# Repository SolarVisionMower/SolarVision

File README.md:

# SolarVision Mower

> [!NOTE]
> *This project is still in development!*

## Project Overview

SolarVision Mower is a YOLO and LiDAR based autonomous lawnmower that we're building for our final capstone engineering project. Once complete, it will feature *fully custom hardware and software*, which includes custom circuitry, firmware, 3D printed or welded components, a modified frame from an existing TORO lawnmower, and much more.

To stay up-to-date with the latest developments, check out the [dev/general][01] branch (specifically the [BACKLOG.md][02] file), to find a detailed list of everything we're doing. It will also help to navigate the various branches and directories (which will most likely grow in complexity as time progresses). Branches will the naming convention `xx/yy` are *permanent* branches, in the category specified by `xx`. Others can be considered temporary only.

## Tech Stack

- Software Tools
    - **KiCAD** - For PCB Design
    - **Fusion360** - For designing 3D models
    - **ESP-IDF** - For firmware programming on the ESP32
    - **STM32CubeMX** - For hardware configuration and initial code generation on the STM32
    - **STM32CubeIDE** - For firmware programming on the STM32
    - **ST Edge AI Suite** - For YOLO model conversion and code generation
- Software Libraries
    - **FreeRTOS** - For multithreading on both microcontrollers
    - **[espressif/arduino-esp32][05]** - For running Arduino functions in the ESP32
    - **[thijses/rplidar][06]** - For ease of integration of the RPLidar A1.
    - **[jh247247/DW1000-fan-video][07]** - Initial firmware implementation for the Ultra Wideband Positioning Modules
- Hardware Tools
    - Fabrication tools from the [NJIT Makerspace][08].
    - Circuit analysis tools from the [NJIT ECE Labs][09].
    - SLogic16U3 Logic Analyzer.
    - [JLCPCB][10] for PCB fabrication

## The Team

- Arnav Revankar
    - **Computer Engineer** - Graduating Dec 2026
    - Responsibilities:
        - Co-Lead Developer, and Manager for Hardware Design.
        - Developed the [STM32N6 Board][03]
        - Oversaw the development of the [Main Board][04]
- Panuha Were
    - **Computer Engineer** - Graduating May 2026
    - Responsibilities:
        - Co-Lead Developer, and Manager for Software Design
        - Contributed to the [Main Board][04] hardware design
        - Overseeing Firmware Development for the ESP32S3
- Layth Younes 
    - **Computer Engineer** - Graduating May 2026
    - Responsibilities:
        - Developer, and Manager for 3D Designs and Fabrication
        - Contributed to the [Main Board][04] hardware design
        - Overseeing the physical design of the frame, and enclosures.
- Daniel Assaf
    - **Computer Engineer** - Graduating May 2026
    - Responsibilities:
        - Developer, and Test/Integration Engineer
        - Contributed to the [Main Board][04] hardware design
        - Contributed to writing Documentation/Reports on progress.

## License

As of date (March 2nd, 2026) we have *not* decided upon a license. All rights are reserved by the authors.

<!-- Links -->
[01]: https://github.com/SolarVision/SolarVisionMower/tree/dev/general
[02]: https://github.com/SolarVision/SolarVisionMower/blob/dev/general/docs/BACKLOG.md
[03]: https://github.com/SolarVision/SolarVisionMower/tree/dev/PCBDesign/Hardware/STM32N6_Board
[04]: https://github.com/SolarVision/SolarVisionMower/tree/dev/MainBoard/Hardware/Main_Board
[05]: https://github.com/espressif/arduino-esp32
[06]: https://github.com/thijses/rplidar
[07]: https://github.com/jh247247/DW1000-fan-video
[08]: https://njitmakerspace.com
[09]: https://ecelabs.njit.edu
[10]: https://jlcpcb.com

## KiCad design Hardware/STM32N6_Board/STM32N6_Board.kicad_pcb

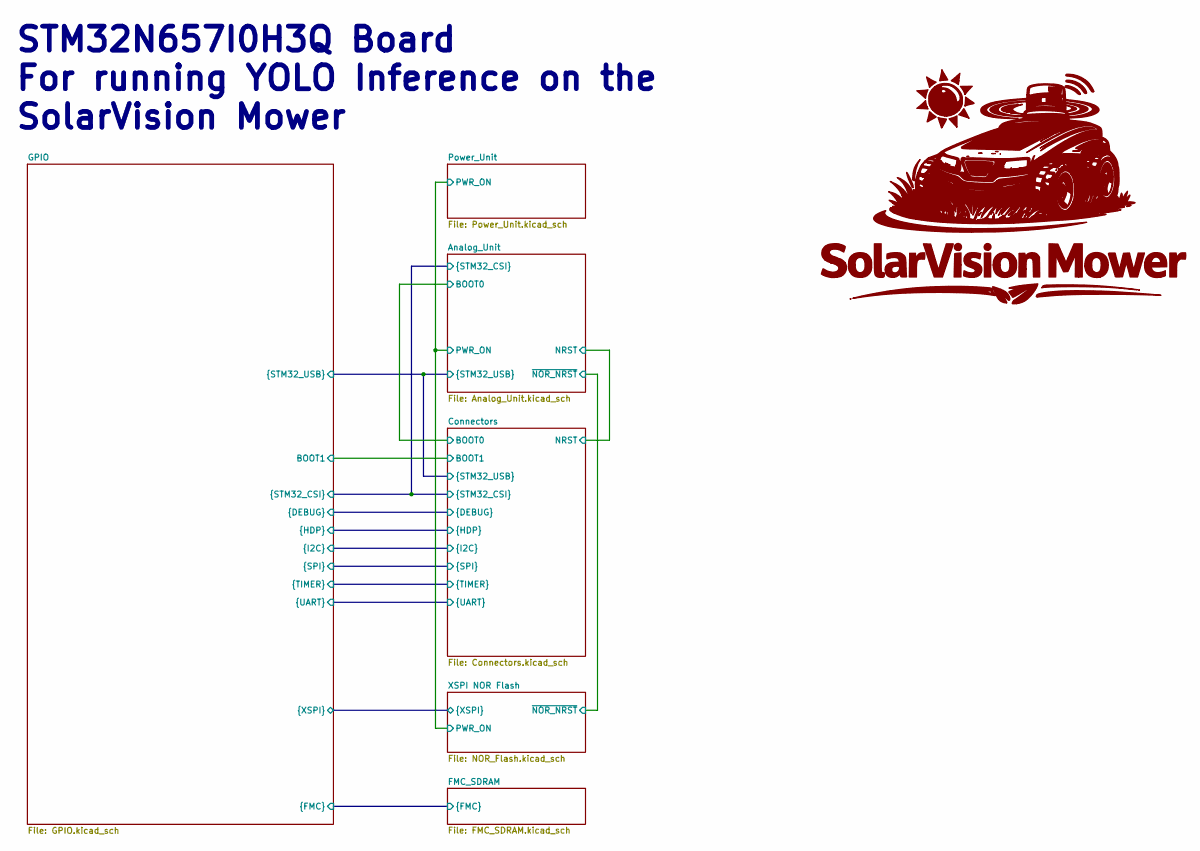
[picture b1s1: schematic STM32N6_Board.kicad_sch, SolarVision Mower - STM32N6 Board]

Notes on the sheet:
STM32N657I0H3Q Board For running YOLO Inference on the SolarVision Mower

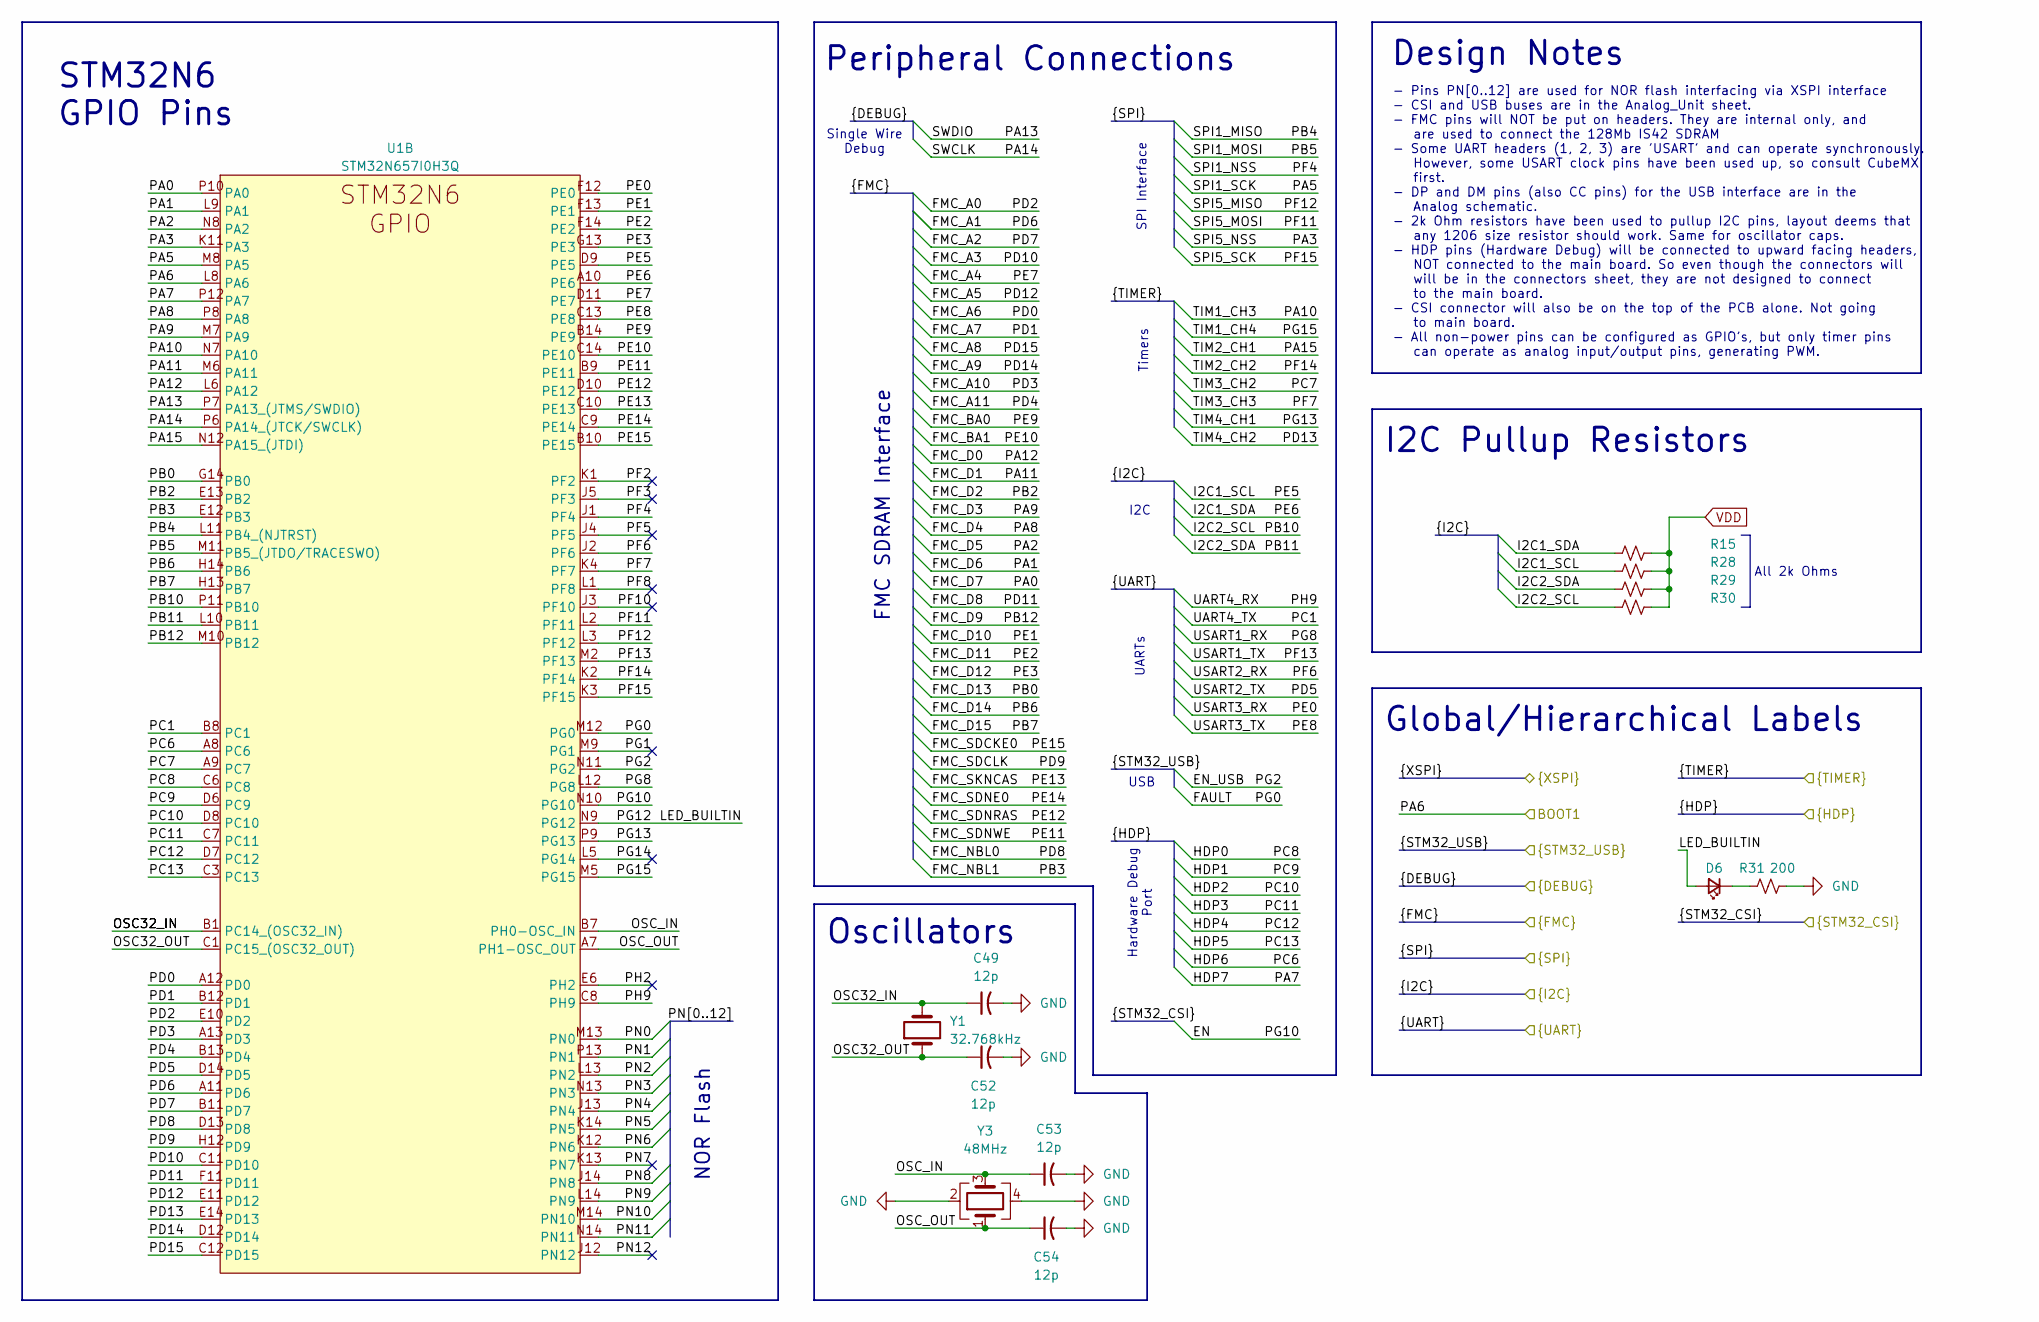
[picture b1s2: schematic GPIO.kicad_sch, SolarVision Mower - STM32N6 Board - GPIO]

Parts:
C49, C52, C53, C54: 12p; C_0402_1005Metric_Pad0.74x0.62mm_HandSolder
D6: LED_Small; LED_0603_1608Metric_Pad1.05x0.95mm_HandSolder
R15, R28, R29, R30: 2k; R_0402_1005Metric
R31: 200; R_0402_1005Metric
U1: STM32N657I0H3Q; STM32N657I0H3Q_VFBGA178_14x14
Y1: 32.768kHz; 32kHz_SC-20S_2Pin_2.05x1.2mm
Y3: 48MHz; 48MHz_Q22FA12800150_4Pin_2.0z1.6mm

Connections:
/Analog_Unit/EN: U1.N10 (PG10); also elsewhere on the board
/Analog_Unit/EN_USB: U1.N11 (PG2); also elsewhere on the board
/Analog_Unit/FAULT: U1.M12 (PG0); also elsewhere on the board
/Connectors/BOOT1: U1.L8 (PA6); also elsewhere on the board
/Connectors/HDP0: U1.C6 (PC8); also elsewhere on the board
/Connectors/HDP1: U1.D6 (PC9); also elsewhere on the board
/Connectors/HDP2: U1.D8 (PC10); also elsewhere on the board
/Connectors/HDP3: U1.C7 (PC11); also elsewhere on the board
/Connectors/HDP4: U1.D7 (PC12); also elsewhere on the board
/Connectors/HDP5: U1.C3 (PC13); also elsewhere on the board
/Connectors/HDP6: U1.A8 (PC6); also elsewhere on the board
/Connectors/HDP7: U1.P12 (PA7); also elsewhere on the board
/Connectors/I2C1_SCL: R28.1, U1.D9 (PE5); also elsewhere on the board
/Connectors/I2C1_SDA: R15.1, U1.A10 (PE6); also elsewhere on the board
/Connectors/I2C2_SCL: R30.1, U1.P11 (PB10); also elsewhere on the board
/Connectors/I2C2_SDA: R29.1, U1.L10 (PB11); also elsewhere on the board
/Connectors/SPI1_MISO: U1.L11 (PB4_(NJTRST)); also elsewhere on the board
/Connectors/SPI1_MOSI: U1.M11 (PB5_(JTDO/TRACESWO)); also elsewhere on the board
/Connectors/SPI1_NSS: U1.J1 (PF4); also elsewhere on the board
/Connectors/SPI1_SCK: U1.M8 (PA5); also elsewhere on the board
/Connectors/SPI5_MISO: U1.L3 (PF12); also elsewhere on the board
/Connectors/SPI5_MOSI: U1.L2 (PF11); also elsewhere on the board
/Connectors/SPI5_NSS: U1.K11 (PA3); also elsewhere on the board
/Connectors/SPI5_SCK: U1.K3 (PF15); also elsewhere on the board
/Connectors/SWCLK: U1.P6 (PA14_(JTCK/SWCLK)); also elsewhere on the board
/Connectors/SWDIO: U1.P7 (PA13_(JTMS/SWDIO)); also elsewhere on the board
/Connectors/TIM1_CH3: U1.N7 (PA10); also elsewhere on the board
/Connectors/TIM1_CH4: U1.M5 (PG15); also elsewhere on the board
/Connectors/TIM2_CH1: U1.N12 (PA15_(JTDI)); also elsewhere on the board
/Connectors/TIM2_CH2: U1.K2 (PF14); also elsewhere on the board
/Connectors/TIM3_CH2: U1.A9 (PC7); also elsewhere on the board
/Connectors/TIM3_CH3: U1.K4 (PF7); also elsewhere on the board
/Connectors/TIM4_CH1: U1.P9 (PG13); also elsewhere on the board
/Connectors/TIM4_CH2: U1.E14 (PD13); also elsewhere on the board
/Connectors/UART4_RX: U1.C8 (PH9); also elsewhere on the board
/Connectors/UART4_TX: U1.B8 (PC1); also elsewhere on the board
/Connectors/USART1_RX: U1.L12 (PG8); also elsewhere on the board
/Connectors/USART1_TX: U1.M2 (PF13); also elsewhere on the board
/Connectors/USART2_RX: U1.J2 (PF6); also elsewhere on the board
/Connectors/USART2_TX: U1.D14 (PD5); also elsewhere on the board
/Connectors/USART3_RX: U1.F12 (PE0); also elsewhere on the board
/Connectors/USART3_TX: U1.C13 (PE8); also elsewhere on the board
/FMC_SDRAM/FMC_A0: U1.E10 (PD2); also elsewhere on the board
/FMC_SDRAM/FMC_A1: U1.A11 (PD6); also elsewhere on the board
/FMC_SDRAM/FMC_A2: U1.B11 (PD7); also elsewhere on the board
/FMC_SDRAM/FMC_A3: U1.C11 (PD10); also elsewhere on the board
/FMC_SDRAM/FMC_A4: U1.D11 (PE7); also elsewhere on the board
/FMC_SDRAM/FMC_A5: U1.E11 (PD12); also elsewhere on the board
/FMC_SDRAM/FMC_A6: U1.A12 (PD0); also elsewhere on the board
/FMC_SDRAM/FMC_A7: U1.B12 (PD1); also elsewhere on the board
/FMC_SDRAM/FMC_A8: U1.C12 (PD15); also elsewhere on the board
/FMC_SDRAM/FMC_A9: U1.D12 (PD14); also elsewhere on the board
/FMC_SDRAM/FMC_A10: U1.A13 (PD3); also elsewhere on the board
/FMC_SDRAM/FMC_A11: U1.B13 (PD4); also elsewhere on the board
/FMC_SDRAM/FMC_BA0: U1.B14 (PE9); also elsewhere on the board
/FMC_SDRAM/FMC_BA1: U1.C14 (PE10); also elsewhere on the board
/FMC_SDRAM/FMC_D0: U1.L6 (PA12); also elsewhere on the board
/FMC_SDRAM/FMC_D1: U1.M6 (PA11); also elsewhere on the board
/FMC_SDRAM/FMC_D2: U1.E13 (PB2); also elsewhere on the board
/FMC_SDRAM/FMC_D3: U1.M7 (PA9); also elsewhere on the board
/FMC_SDRAM/FMC_D4: U1.P8 (PA8); also elsewhere on the board
/FMC_SDRAM/FMC_D5: U1.N8 (PA2); also elsewhere on the board
/FMC_SDRAM/FMC_D6: U1.L9 (PA1); also elsewhere on the board
/FMC_SDRAM/FMC_D7: U1.P10 (PA0); also elsewhere on the board
/FMC_SDRAM/FMC_D8: U1.F11 (PD11); also elsewhere on the board
/FMC_SDRAM/FMC_D9: U1.M10 (PB12); also elsewhere on the board
/FMC_SDRAM/FMC_D10: U1.F13 (PE1); also elsewhere on the board
/FMC_SDRAM/FMC_D11: U1.F14 (PE2); also elsewhere on the board
/FMC_SDRAM/FMC_D12: U1.G13 (PE3); also elsewhere on the board
/FMC_SDRAM/FMC_D13: U1.G14 (PB0); also elsewhere on the board
/FMC_SDRAM/FMC_D14: U1.H14 (PB6); also elsewhere on the board
/FMC_SDRAM/FMC_D15: U1.H13 (PB7); also elsewhere on the board
/FMC_SDRAM/FMC_NBL0: U1.D13 (PD8); also elsewhere on the board
/FMC_SDRAM/FMC_NBL1: U1.E12 (PB3); also elsewhere on the board
/FMC_SDRAM/FMC_SDCKE0: U1.B10 (PE15); also elsewhere on the board
/FMC_SDRAM/FMC_SDCLK: U1.H12 (PD9); also elsewhere on the board
/FMC_SDRAM/FMC_SDNE0: U1.C9 (PE14); also elsewhere on the board
/FMC_SDRAM/FMC_SDNRAS: U1.D10 (PE12); also elsewhere on the board
/FMC_SDRAM/FMC_SDNWE: U1.B9 (PE11); also elsewhere on the board
/FMC_SDRAM/FMC_SKNCAS: U1.C10 (PE13); also elsewhere on the board
/GPIO/LED_BUILTIN: D6.2 (A), U1.N9 (PG12)
/GPIO/OSC32_IN: C49.1, U1.B1 (PC14_(OSC32_IN)), Y1.2
/GPIO/OSC32_OUT: C52.1, U1.C1 (PC15_(OSC32_OUT)), Y1.1
/GPIO/OSC_IN: C53.1, U1.B7 (PH0-OSC_IN), Y3.3
/GPIO/OSC_OUT: C54.1, U1.A7 (PH1-OSC_OUT), Y3.1
/GPIO/PF2: U1.K1 (PF2)
/GPIO/PF3: U1.J5 (PF3)
/GPIO/PF5: U1.J4 (PF5)
/GPIO/PF8: U1.L1 (PF8)
/GPIO/PF10: U1.J3 (PF10)
/GPIO/PG1: U1.M9 (PG1)
/GPIO/PG14: U1.L5 (PG14)
/GPIO/PH2: U1.E6 (PH2)
/GPIO/PN0: U1.M13 (PN0); also elsewhere on the board
/GPIO/PN1: U1.P13 (PN1); also elsewhere on the board
/GPIO/PN2: U1.L13 (PN2); also elsewhere on the board
/GPIO/PN3: U1.N13 (PN3); also elsewhere on the board
/GPIO/PN4: U1.J13 (PN4); also elsewhere on the board
/GPIO/PN5: U1.K14 (PN5); also elsewhere on the board
/GPIO/PN6: U1.K12 (PN6); also elsewhere on the board
/GPIO/PN7: U1.K13 (PN7)
/GPIO/PN8: U1.J14 (PN8); also elsewhere on the board
/GPIO/PN9: U1.L14 (PN9); also elsewhere on the board
/GPIO/PN10: U1.M14 (PN10); also elsewhere on the board
/GPIO/PN11: U1.N14 (PN11); also elsewhere on the board
/GPIO/PN12: U1.J12 (PN12)
GND: C49.2, C52.2, C53.2, C54.2, R31.2, Y3.2, Y3.4; also elsewhere on the board
unnamed: D6.1 (K), R31.1
VDD: R15.2, R28.2, R29.2, R30.2; also elsewhere on the board

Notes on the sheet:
I2C
Global/Hierarchical Labels
Timers
FMC SDRAM Interface
- Pins PN[0..12] are used for NOR flash interfacing via XSPI interface - CSI and USB buses are in the Analog_Unit sheet. - FMC pins will NOT be put on headers. They are internal only, and are used to connect the 128Mb IS42 SDRAM - Some UART headers (1, 2, 3) are 'USART' and can operate synchronousl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
STM32N6 GPIO Pins
I2C Pullup Resistors
UARTs
Peripheral Connections
Oscillators
USB
Hardware Debug Port
NOR Flash
All 2k Ohms
Single Wire Debug
SPI Interface
Design Notes

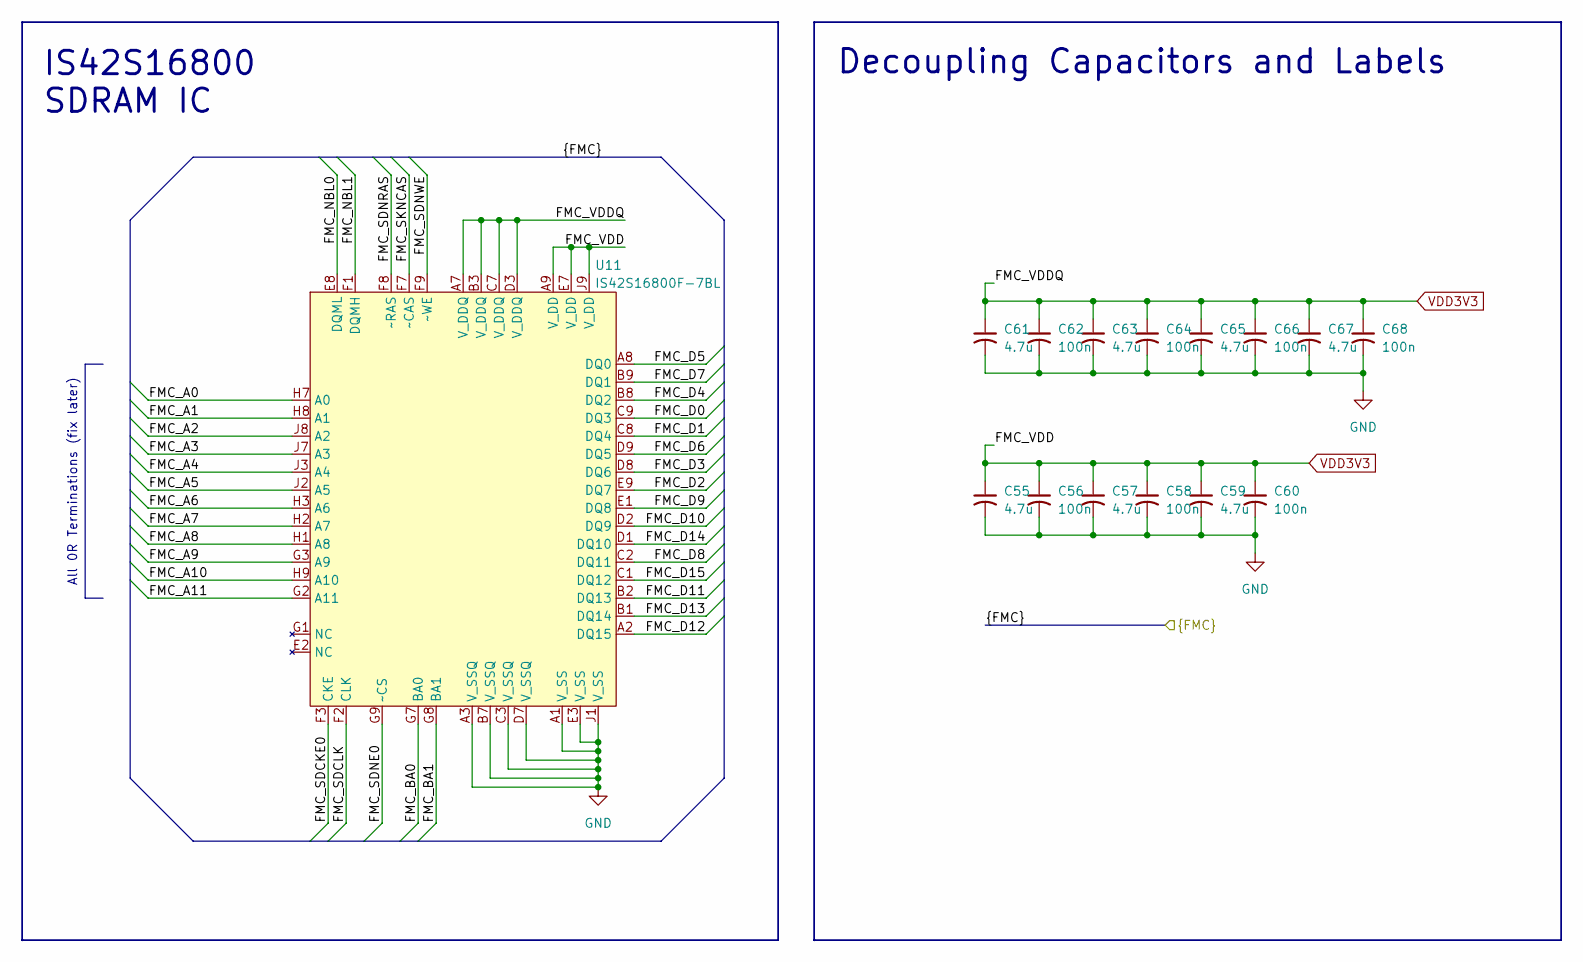
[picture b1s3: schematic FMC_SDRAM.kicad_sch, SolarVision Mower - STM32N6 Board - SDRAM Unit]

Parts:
C55, C57, C59, C61, C63, C65, C67: 4.7u; C_0402_1005Metric
C56, C58, C60, C62, C64, C66, C68: 100n; C_0402_1005Metric
U11: IS42S16800F-7BL; IS42S16800F-7BL_BGA54C80P9X9_800X800X120

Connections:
/FMC_SDRAM/FMC_A0: U11.H7 (A0); also elsewhere on the board
/FMC_SDRAM/FMC_A1: U11.H8 (A1); also elsewhere on the board
/FMC_SDRAM/FMC_A2: U11.J8 (A2); also elsewhere on the board
/FMC_SDRAM/FMC_A3: U11.J7 (A3); also elsewhere on the board
/FMC_SDRAM/FMC_A4: U11.J3 (A4); also elsewhere on the board
/FMC_SDRAM/FMC_A5: U11.J2 (A5); also elsewhere on the board
/FMC_SDRAM/FMC_A6: U11.H3 (A6); also elsewhere on the board
/FMC_SDRAM/FMC_A7: U11.H2 (A7); also elsewhere on the board
/FMC_SDRAM/FMC_A8: U11.H1 (A8); also elsewhere on the board
/FMC_SDRAM/FMC_A9: U11.G3 (A9); also elsewhere on the board
/FMC_SDRAM/FMC_A10: U11.H9 (A10); also elsewhere on the board
/FMC_SDRAM/FMC_A11: U11.G2 (A11); also elsewhere on the board
/FMC_SDRAM/FMC_BA0: U11.G7 (BA0); also elsewhere on the board
/FMC_SDRAM/FMC_BA1: U11.G8 (BA1); also elsewhere on the board
/FMC_SDRAM/FMC_D0: U11.C9 (DQ3); also elsewhere on the board
/FMC_SDRAM/FMC_D1: U11.C8 (DQ4); also elsewhere on the board
/FMC_SDRAM/FMC_D2: U11.E9 (DQ7); also elsewhere on the board
/FMC_SDRAM/FMC_D3: U11.D8 (DQ6); also elsewhere on the board
/FMC_SDRAM/FMC_D4: U11.B8 (DQ2); also elsewhere on the board
/FMC_SDRAM/FMC_D5: U11.A8 (DQ0); also elsewhere on the board
/FMC_SDRAM/FMC_D6: U11.D9 (DQ5); also elsewhere on the board
/FMC_SDRAM/FMC_D7: U11.B9 (DQ1); also elsewhere on the board
/FMC_SDRAM/FMC_D8: U11.C2 (DQ11); also elsewhere on the board
/FMC_SDRAM/FMC_D9: U11.E1 (DQ8); also elsewhere on the board
/FMC_SDRAM/FMC_D10: U11.D2 (DQ9); also elsewhere on the board
/FMC_SDRAM/FMC_D11: U11.B2 (DQ13); also elsewhere on the board
/FMC_SDRAM/FMC_D12: U11.A2 (DQ15); also elsewhere on the board
/FMC_SDRAM/FMC_D13: U11.B1 (DQ14); also elsewhere on the board
/FMC_SDRAM/FMC_D14: U11.D1 (DQ10); also elsewhere on the board
/FMC_SDRAM/FMC_D15: U11.C1 (DQ12); also elsewhere on the board
/FMC_SDRAM/FMC_NBL0: U11.E8 (DQML); also elsewhere on the board
/FMC_SDRAM/FMC_NBL1: U11.F1 (DQMH); also elsewhere on the board
/FMC_SDRAM/FMC_SDCKE0: U11.F3 (CKE); also elsewhere on the board
/FMC_SDRAM/FMC_SDCLK: U11.F2 (CLK); also elsewhere on the board
/FMC_SDRAM/FMC_SDNE0: U11.G9 (~CS); also elsewhere on the board
/FMC_SDRAM/FMC_SDNRAS: U11.F8 (~RAS); also elsewhere on the board
/FMC_SDRAM/FMC_SDNWE: U11.F9 (~WE); also elsewhere on the board
/FMC_SDRAM/FMC_SKNCAS: U11.F7 (~CAS); also elsewhere on the board
GND: C55.2, C56.2, C57.2, C58.2, C59.2, C60.2, C61.2, C62.2, C63.2, C64.2, C65.2, C66.2, C67.2, C68.2, U11.A1 (V_SS), U11.A3 (V_SSQ), U11.B7 (V_SSQ), U11.C3 (V_SSQ), U11.D7 (V_SSQ), U11.E3 (V_SS), U11.J1 (V_SS); also elsewhere on the board
VDD3V3: C55.1, C56.1, C57.1, C58.1, C59.1, C60.1, C61.1, C62.1, C63.1, C64.1, C65.1, C66.1, C67.1, C68.1, U11.A7 (V_DDQ), U11.A9 (V_DD), U11.B3 (V_DDQ), U11.C7 (V_DDQ), U11.D3 (V_DDQ), U11.E7 (V_DD), U11.J9 (V_DD); also elsewhere on the board

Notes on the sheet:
All 0R Terminations (fix later)
IS42S16800 SDRAM IC
Decoupling Capacitors and Labels

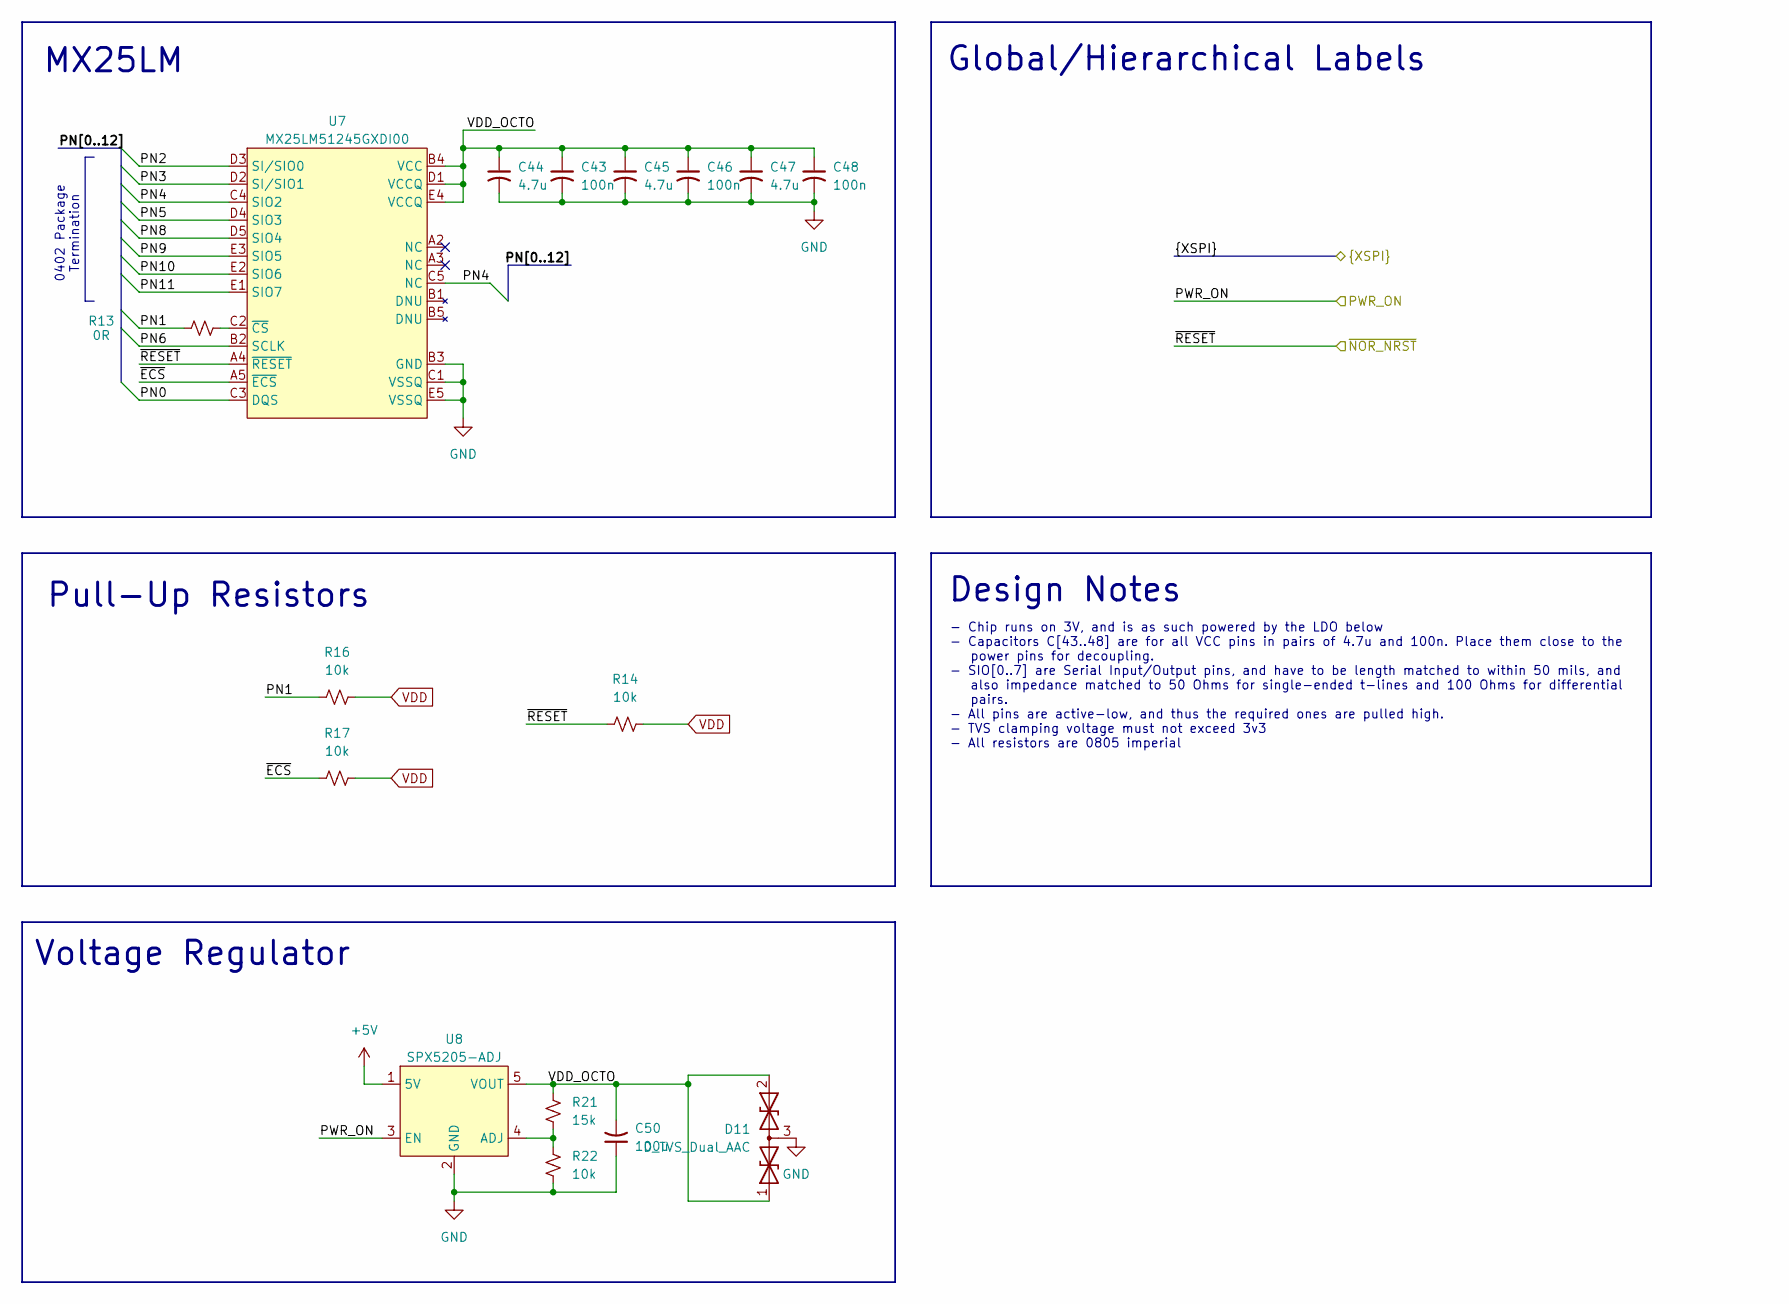
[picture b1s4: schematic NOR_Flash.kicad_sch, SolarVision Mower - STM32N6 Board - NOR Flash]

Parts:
C43, C46, C48: 100n; C_0402_1005Metric
C44, C45, C47: 4.7u; C_0402_1005Metric
C50: 100u; C_0805_2012Metric_Pad1.18x1.45mm_HandSolder
D11: D_TVS_Dual_AAC; SOT-723
R13: 0R; R_0402_1005Metric
R14, R16, R17: 10k; R_0402_1005Metric
R21: 15k; R_0805_2012Metric_Pad1.20x1.40mm_HandSolder
R22: 10k; R_0805_2012Metric_Pad1.20x1.40mm_HandSolder
U7: MX25LM51245GXDI00; MX25LM51245GXD100_BGA24C100P5X5_600X800X120
U8: SPX5205-ADJ; SOT-23-5

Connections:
+5V: U8.1 (5V); also elsewhere on the board
/Analog_Unit/NRST: R14.1, U7.A4 (~RESET); also elsewhere on the board
/Analog_Unit/PWR_ON: U8.3 (EN); also elsewhere on the board
/GPIO/PN0: U7.C3 (DQS); also elsewhere on the board
/GPIO/PN1: R13.1, R16.1; also elsewhere on the board
/GPIO/PN2: U7.D3 (SI/SIO0); also elsewhere on the board
/GPIO/PN3: U7.D2 (SI/SIO1); also elsewhere on the board
/GPIO/PN4: U7.C4 (SIO2), U7.C5 (NC); also elsewhere on the board
/GPIO/PN5: U7.D4 (SIO3); also elsewhere on the board
/GPIO/PN6: U7.B2 (SCLK); also elsewhere on the board
/GPIO/PN8: U7.D5 (SIO4); also elsewhere on the board
/GPIO/PN9: U7.E3 (SIO5); also elsewhere on the board
/GPIO/PN10: U7.E2 (SIO6); also elsewhere on the board
/GPIO/PN11: U7.E1 (SIO7); also elsewhere on the board
/XSPI NOR Flash/VDD_OCTO: C43.1, C44.1, C45.1, C46.1, C47.1, C48.1, C50.2, D11.1 (A1), D11.2 (A2), R21.1, U7.B4 (VCC), U7.D1 (VCCQ), U7.E4 (VCCQ), U8.5 (VOUT)
/XSPI NOR Flash/~ECS: R17.1, U7.A5 (~ECS)
GND: C43.2, C44.2, C45.2, C46.2, C47.2, C48.2, C50.1, D11.3 (common), R22.2, U7.B3 (GND), U7.C1 (VSSQ), U7.E5 (VSSQ), U8.2 (GND); also elsewhere on the board
unnamed: R13.2, U7.C2 (~CS)
unnamed: R21.2, R22.1, U8.4 (ADJ)
VDD: R14.2, R16.2, R17.2; also elsewhere on the board

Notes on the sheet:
- Chip runs on 3V, and is as such powered by the LDO below - Capacitors C[43..48] are for all VCC pins in pairs of 4.7u and 100n. Place them close to the power pins for decoupling. - SIO[0..7] are Serial Input/Output pins, and have to be length matched to within 50 mils, and also impedance matched 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
MX25LM
Global/Hierarchical Labels
Pull-Up Resistors
Voltage Regulator
0402 Package Termination
Design Notes

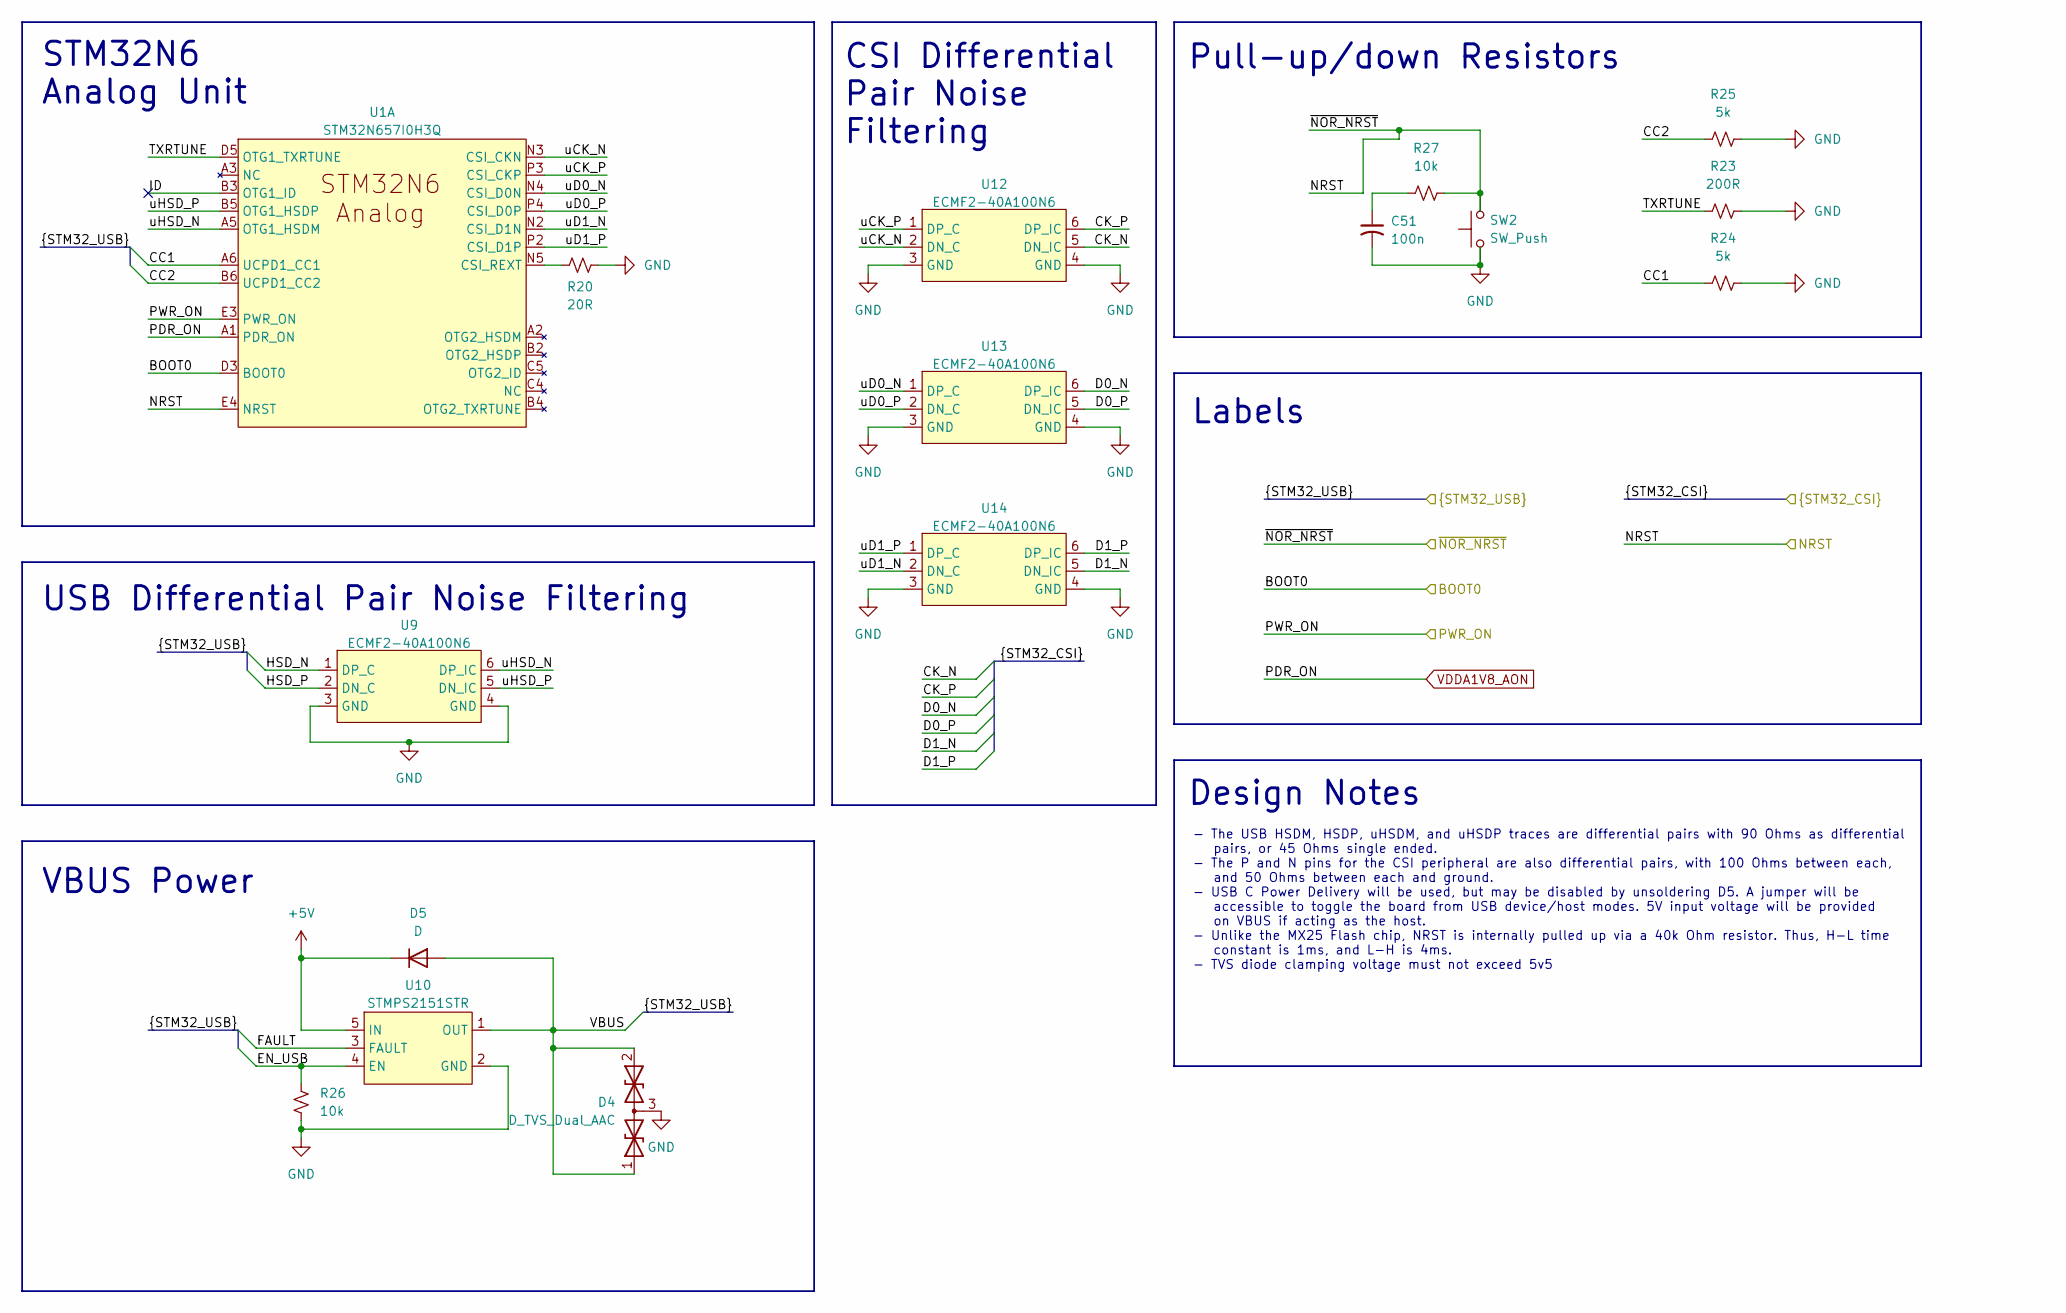
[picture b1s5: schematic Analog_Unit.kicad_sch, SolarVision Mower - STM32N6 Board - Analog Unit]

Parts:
C51: 100n; C_0805_2012Metric_Pad1.18x1.45mm_HandSolder
D4: D_TVS_Dual_AAC; SOT-723
D5: D; LED_0805_2012Metric_Pad1.15x1.40mm_HandSolder
R20: 20R; R_0402_1005Metric
R23: 200R; R_0402_1005Metric
R24, R25: 5k; R_0402_1005Metric
R26: 10k; R_0402_1005Metric
R27: 10k; R_0805_2012Metric_Pad1.20x1.40mm_HandSolder
SW2: SW_Push; SW_SPST_Omron_B3FS-101xP
U1: STM32N657I0H3Q; STM32N657I0H3Q_VFBGA178_14x14
U9, U12, U13, U14: ECMF2-40A100N6; ST_UQFN-6L_1.5x1.7mm_P0.5mm
U10: STMPS2151STR; SOT-23-5

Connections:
+5V: D5.1 (K), U10.5 (IN); also elsewhere on the board
/Analog_Unit/BOOT0: U1.D3 (BOOT0); also elsewhere on the board
/Analog_Unit/CC1: R24.1, U1.A6 (UCPD1_CC1); also elsewhere on the board
/Analog_Unit/CC2: R25.1, U1.B6 (UCPD1_CC2); also elsewhere on the board
/Analog_Unit/CK_N: U12.5 (DN_IC); also elsewhere on the board
/Analog_Unit/CK_P: U12.6 (DP_IC); also elsewhere on the board
/Analog_Unit/D0_N: U13.6 (DP_IC); also elsewhere on the board
/Analog_Unit/D0_P: U13.5 (DN_IC); also elsewhere on the board
/Analog_Unit/D1_N: U14.5 (DN_IC); also elsewhere on the board
/Analog_Unit/D1_P: U14.6 (DP_IC); also elsewhere on the board
/Analog_Unit/EN_USB: R26.2, U10.4 (EN); also elsewhere on the board
/Analog_Unit/FAULT: U10.3 (FAULT); also elsewhere on the board
/Analog_Unit/HSD_N: U9.1 (DP_C); also elsewhere on the board
/Analog_Unit/HSD_P: U9.2 (DN_C); also elsewhere on the board
/Analog_Unit/ID: U1.B3 (OTG1_ID)
/Analog_Unit/NRST: R27.2, SW2.2, U1.E4 (NRST); also elsewhere on the board
/Analog_Unit/PWR_ON: U1.E3 (PWR_ON); also elsewhere on the board
/Analog_Unit/TXRTUNE: R23.1, U1.D5 (OTG1_TXRTUNE)
/Analog_Unit/VBUS: D4.1 (A1), D4.2 (A2), D5.2 (A), U10.1 (OUT); also elsewhere on the board
/Analog_Unit/uCK_N: U1.N3 (CSI_CKN), U12.2 (DN_C)
/Analog_Unit/uCK_P: U1.P3 (CSI_CKP), U12.1 (DP_C)
/Analog_Unit/uD0_N: U1.N4 (CSI_D0N), U13.1 (DP_C)
/Analog_Unit/uD0_P: U1.P4 (CSI_D0P), U13.2 (DN_C)
/Analog_Unit/uD1_N: U1.N2 (CSI_D1N), U14.2 (DN_C)
/Analog_Unit/uD1_P: U1.P2 (CSI_D1P), U14.1 (DP_C)
/Analog_Unit/uHSD_N: U1.A5 (OTG1_HSDM), U9.6 (DP_IC)
/Analog_Unit/uHSD_P: U1.B5 (OTG1_HSDP), U9.5 (DN_IC)
GND: C51.2, D4.3 (common), R20.2, R23.2, R24.2, R25.2, R26.1, SW2.1, U9.3 (GND), U9.4 (GND), U10.2 (GND), U12.3 (GND), U12.4 (GND), U13.3 (GND), U13.4 (GND), U14.3 (GND), U14.4 (GND); also elsewhere on the board
unnamed: C51.1, R27.1
unnamed: R20.1, U1.N5 (CSI_REXT)
VDDA1V8_AON: U1.A1 (PDR_ON); also elsewhere on the board

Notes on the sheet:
VBUS Power
USB Differential Pair Noise Filtering
Design Notes
- The USB HSDM, HSDP, uHSDM, and uHSDP traces are differential pairs with 90 Ohms as differential pairs, or 45 Ohms single ended. - The P and N pins for the CSI peripheral are also differential pairs, with 100 Ohms between each, and 50 Ohms between each and ground. - USB C Power Delivery will be us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
CSI Differential Pair Noise Filtering
Pull-up/down Resistors
STM32N6 Analog Unit
Labels
